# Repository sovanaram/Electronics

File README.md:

# Isolated Pure Sine Wave Single Phase Inverter using SPWM
this topic is about How to make Inverter by your self and These are the steps to makes it:
1, Researching theories of Inverter 
2, Select Topology (DCDC Converter stage, Inverter stage)
3, Calculating DCDC Converter and Inverter
4, Calculating Transformer and Inductors of DCDC Converter
5, Design Transformer and Inductors 
6, Design schematic and PCB 
7, Installing Hardware 
8, Select electronic switches(MOSFETs and DIODEs)
9, Select Controller
10, Programming and choose the types of Closed loop Control Methods, Filter
11, Testing Hardware

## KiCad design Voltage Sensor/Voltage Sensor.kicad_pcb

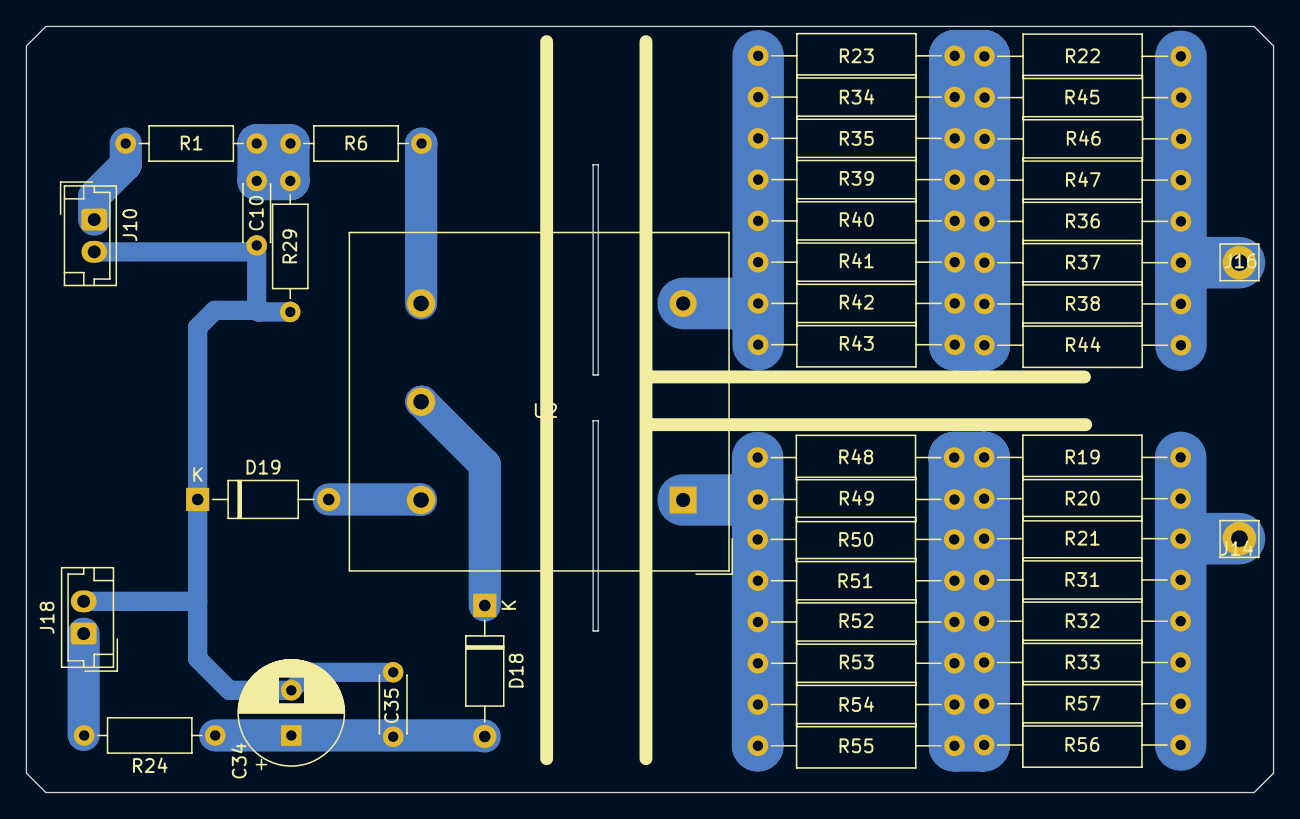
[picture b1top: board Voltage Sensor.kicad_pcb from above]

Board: 2 copper layers, 96.7 x 59.4 mm, 46 parts (0 on the bottom side), 4 nets.

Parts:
C10: 102; C_Disc_D4.3mm_W1.9mm_P5.00mm
C34: 100uF/25; CP_Radial_D8.0mm_P3.50mm
C35: 104; C_Disc_D4.3mm_W1.9mm_P5.00mm
D18: 1N4007; D_A-405_P10.16mm_Horizontal
D19: D; D_A-405_P10.16mm_Horizontal
J10: V_sens; JST_EH_B2B-EH-A_1x02_P2.50mm_Vertical
J14: 400VDC; Pin_D1.3mm_L11.3mm_W2.8mm_Flat
J16: GND; Pin_D1.3mm_L11.3mm_W2.8mm_Flat
J18: 12V_Vsens; JST_EH_B2B-EH-A_1x02_P2.50mm_Vertical
R1: 330; R_Axial_DIN0207_L6.3mm_D2.5mm_P10.16mm_Horizontal
R6, R29: 1K; R_Axial_DIN0207_L6.3mm_D2.5mm_P10.16mm_Horizontal
R19, R20, R21, R22, R23, R31, R32, R33, R34, R35, R36, R37, R38, R39, R40, R41, R42, R43, R44, R45, R46, R47, R48, R49, R50, R51, R52, R53, R54, R55, R56, R57: 100k; R_Axial_DIN0309_L9.0mm_D3.2mm_P15.24mm_Horizontal
R24: 100; R_Axial_DIN0207_L6.3mm_D2.5mm_P10.16mm_Horizontal
U2: LV25-P; LEM_LV25-P

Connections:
+12V: J18.1, R24.2
/+400VDC: J14.1, R19.2, R20.2, R21.2, R31.2, R32.2, R33.2, R56.2, R57.2
GND: C10.2, C34.2, C35.2, D19.1 (K), J10.2, J18.2, R29.1
GND1: J16.1, R22.2, R36.2, R37.2, R38.2, R44.2, R45.2, R46.2, R47.2

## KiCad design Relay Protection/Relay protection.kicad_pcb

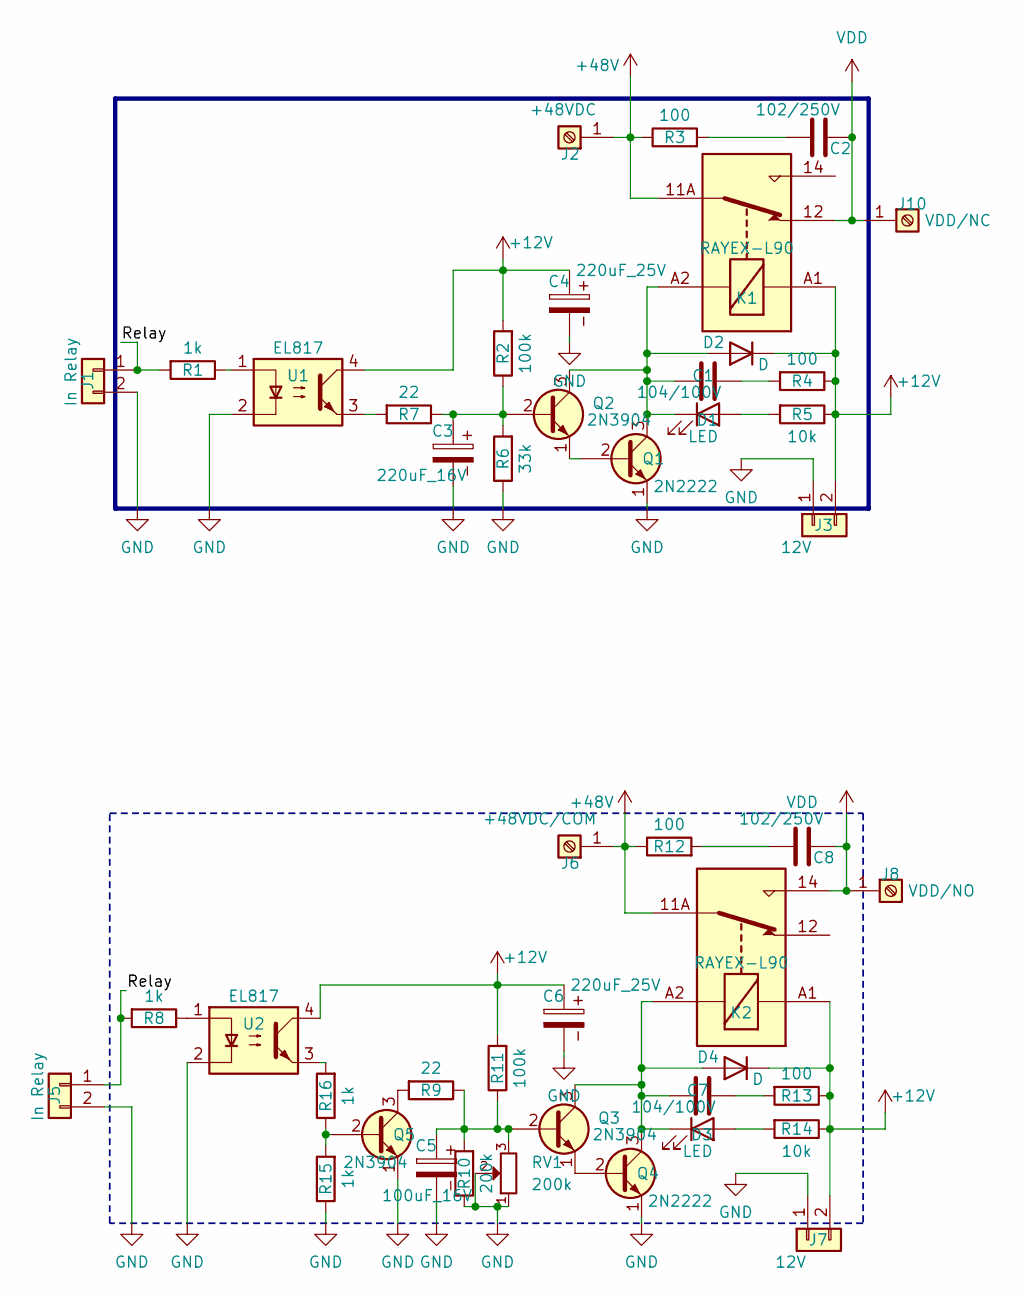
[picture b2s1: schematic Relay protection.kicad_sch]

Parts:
C1, C7: 104/100V; C_Disc_D6.0mm_W2.5mm_P5.00mm
C2, C8: 102/250V; Fuse_BelFuse_0ZRE0016FF_L9.9mm_W3.8mm
C3: 220uF_16V; CP_Radial_D6.3mm_P2.50mm
C4, C6: 220uF_25V; CP_Radial_D6.3mm_P2.50mm
C5: 100uF_16V; CP_Radial_D6.3mm_P2.50mm
D1, D3: LED; LED_D5.0mm_Clear
D2, D4: D; D_A-405_P10.16mm_Horizontal
J1, J5: In Relay; JST_EH_B2B-EH-A_1x02_P2.50mm_Vertical
J2: +48VDC; TerminalBlock_MetzConnect_360291_1x01_Horizontal_ScrewM3.0_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
J3, J7: 12V; JST_EH_B2B-EH-A_1x02_P2.50mm_Vertical
J6: +48VDC/COM; TerminalBlock_MetzConnect_360291_1x01_Horizontal_ScrewM3.0_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
J8: VDD/NO; TerminalBlock_MetzConnect_360291_1x01_Horizontal_ScrewM3.0_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
J10: VDD/NC; TerminalBlock_MetzConnect_360291_1x01_Horizontal_ScrewM3.0_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
K1, K2: RAYEX-L90; Relay_SPDT_RAYEX-L90
Q1, Q4: 2N2222; TO-92_Inline_Wide
Q2, Q3, Q5: 2N3904; TO-92L_Inline_Wide
R1, R8, R15, R16: 1k; R_Axial_DIN0207_L6.3mm_D2.5mm_P10.16mm_Horizontal
R2, R11: 100k; R_Axial_DIN0207_L6.3mm_D2.5mm_P10.16mm_Horizontal
R3, R4, R12, R13: 100; R_Axial_DIN0207_L6.3mm_D2.5mm_P10.16mm_Horizontal
R5, R14: 10k; R_Axial_DIN0207_L6.3mm_D2.5mm_P10.16mm_Horizontal
R6: 33k; R_Axial_DIN0207_L6.3mm_D2.5mm_P10.16mm_Horizontal
R7, R9: 22; R_Axial_DIN0207_L6.3mm_D2.5mm_P10.16mm_Horizontal
R10: 200k; R_Axial_DIN0207_L6.3mm_D2.5mm_P10.16mm_Horizontal
RV1: 200k; Potentiometer_RM065
U1, U2: EL817; DIP-4_W7.62mm

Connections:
+12V: C4.1, C6.1, D2.1 (K), D4.1 (K), J3.2, J7.2, K1.A1, K2.A1, R2.2, R4.1, R5.1, R11.2, R13.1, R14.1, U1.4, U2.4
+48V: J2.1, J6.1, K1.11A, K1.11B, K2.11A, K2.11B, R3.1, R12.1
/Relay: J1.1, J5.1, R1.2, R8.2
GND: C3.2, C4.2, C5.2, C6.2, J1.2, J3.1, J5.2, J7.1, Q1.1 (E), Q4.1 (E), Q5.1 (E), R6.1, R10.1, R15.1, RV1.1, RV1.2, U1.2, U2.2
unnamed: C1.1, R4.2
unnamed: C2.1, R3.2
unnamed: C7.1, R13.2
unnamed: C8.1, R12.2
unnamed: D1.2 (A), R5.2
unnamed: C1.2, D1.1 (K), D2.2 (A), K1.A2, Q1.3 (C), Q2.3 (C)
unnamed: D3.2 (A), R14.2
unnamed: C7.2, D3.1 (K), D4.2 (A), K2.A2, Q3.3 (C), Q4.3 (C)
unnamed: Q1.2 (B), Q2.1 (E)
unnamed: C3.1, Q2.2 (B), R2.1, R6.2, R7.1
unnamed: C5.1, Q3.2 (B), R9.1, R10.2, R11.1, RV1.3
unnamed: Q3.1 (E), Q4.2 (B)
unnamed: Q5.2 (B), R15.2, R16.1
unnamed: Q5.3 (C), R9.2
unnamed: R1.1, U1.1
unnamed: R7.2, U1.3
unnamed: R8.1, U2.1
unnamed: R16.2, U2.3
VDD: C2.2, C8.2, J8.1, J10.1, K1.12, K2.14

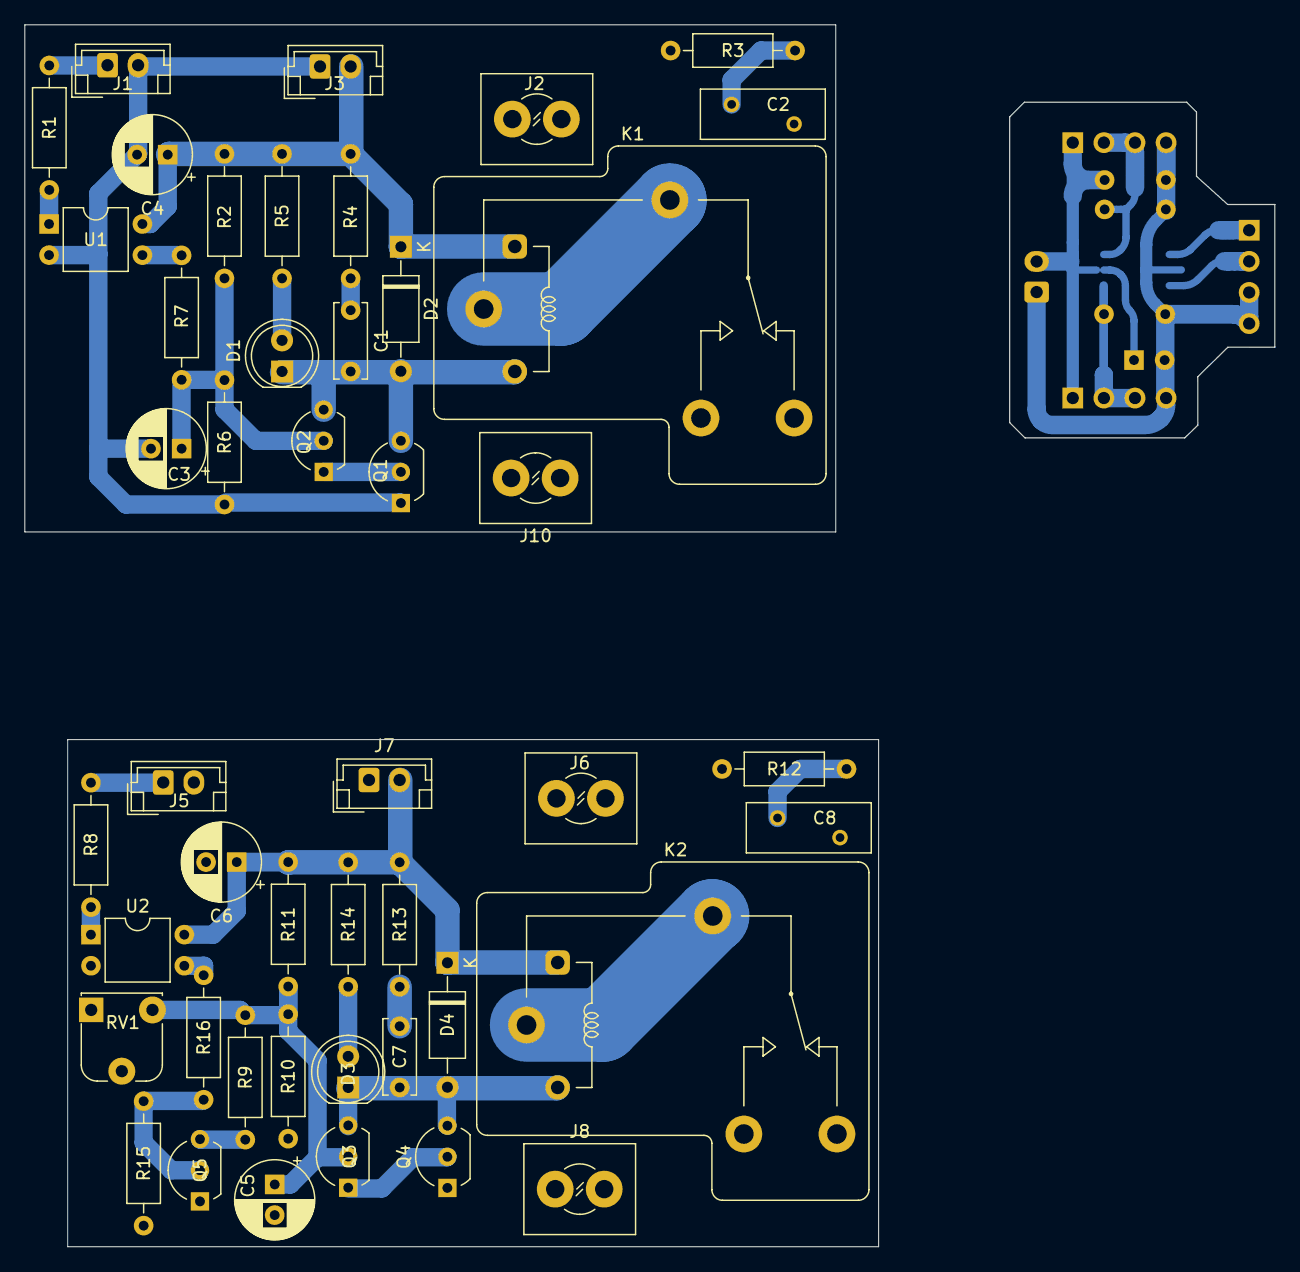
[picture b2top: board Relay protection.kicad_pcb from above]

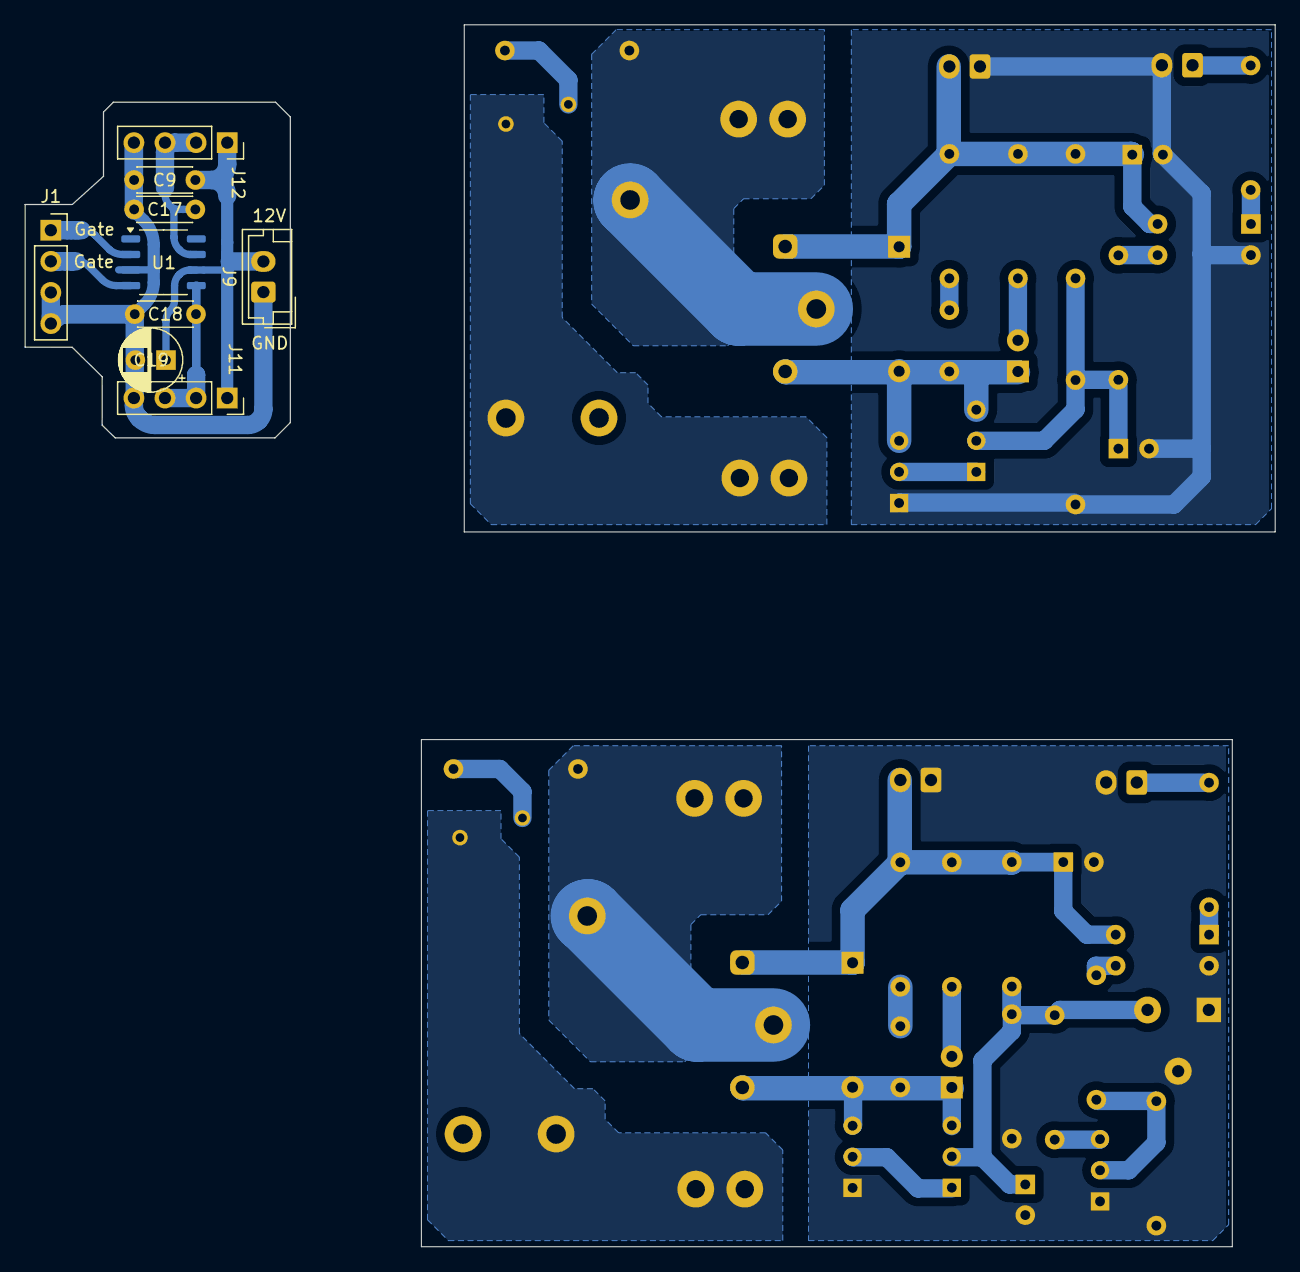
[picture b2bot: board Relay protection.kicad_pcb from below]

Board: 2 copper layers, 102.1 x 99.8 mm, 55 parts (9 on the bottom side), 23 nets.

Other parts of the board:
C9: 104; C_Disc_D4.3mm_W1.9mm_P5.00mm
C17, C18: 102; C_Disc_D4.3mm_W1.9mm_P5.00mm
C19: 10uF/50V; CP_Radial_D5.0mm_P2.50mm
J1#2, J11, J12: Conn_01x04; PinSocket_1x04_P2.54mm_Vertical
J9: 12V Gdriver; JST_EH_B2B-EH-A_1x02_P2.50mm_Vertical
U1#2: IRS4427S; SSOP-8_3.9x5.05mm_P1.27mm

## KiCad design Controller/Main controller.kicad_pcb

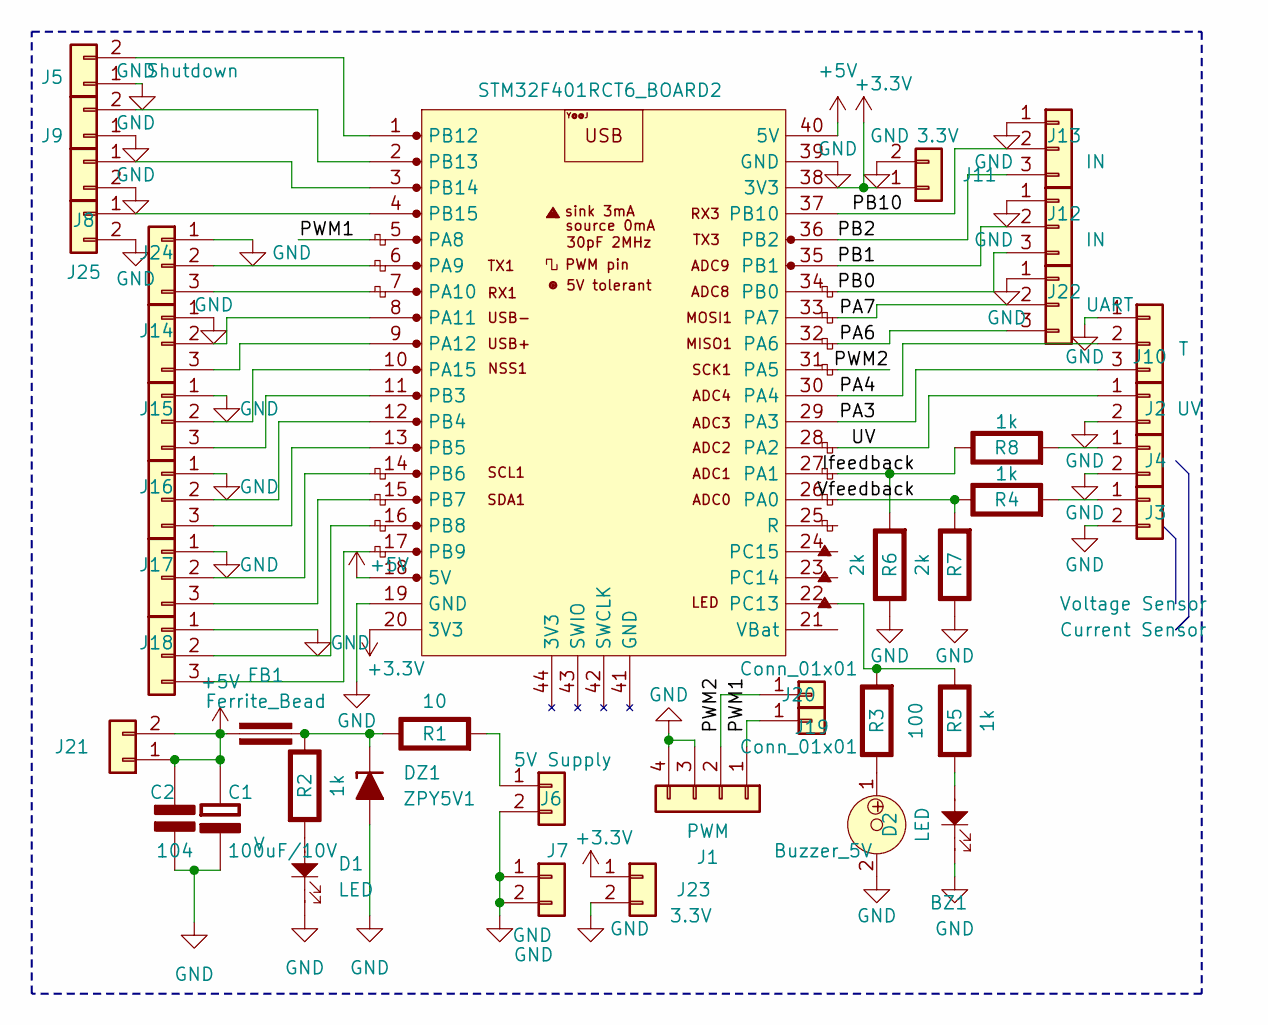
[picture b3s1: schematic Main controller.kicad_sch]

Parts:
BZ1: Buzzer_5V; MagneticBuzzer_ProSignal_ABT-410-RC
C1: 100uF/10V; CP_Radial_D7.5mm_P2.50mm; Rating V
C2: 104; C_Disc_D5.0mm_W2.5mm_P5.00mm; Rating V
D1, D2: LED; LED_D5.0mm
DZ1: ZPY5V1; D_DO-34_SOD68_P7.62mm_Horizontal
FB1: Ferrite_Bead; L_Axial_L7.0mm_D3.3mm_P5.08mm_Vertical_Fastron_MICC
J1: PWM; JST_EH_B4B-EH-A_1x04_P2.50mm_Vertical
J2: UV; JST_EH_B2B-EH-A_1x02_P2.50mm_Vertical
J3: Voltage Sensor; JST_EH_B2B-EH-A_1x02_P2.50mm_Vertical
J4: Current Sensor; JST_EH_B2B-EH-A_1x02_P2.50mm_Vertical
J5: Shutdown; JST_EH_B2B-EH-A_1x02_P2.50mm_Vertical
J6: 5V Supply; JST_EH_B2B-EH-A_1x02_P2.50mm_Vertical
J7: GND; JST_EH_B2B-EH-A_1x02_P2.50mm_Vertical
J8, J9, J21, J25: JST_EH_B2B-EH-A_1x02_P2.50mm_Vertical
J10: T; JST_EH_B3B-EH-A_1x03_P2.50mm_Vertical
J11, J23: 3.3V; JST_EH_B2B-EH-A_1x02_P2.50mm_Vertical
J12, J13: IN; JST_EH_B3B-EH-A_1x03_P2.50mm_Vertical
J14, J15, J16, J17, J18, J24: JST_EH_B3B-EH-A_1x03_P2.50mm_Vertical
J19, J20: Conn_01x01; PinSocket_1x01_P2.54mm_Vertical
J22: UART; JST_EH_B3B-EH-A_1x03_P2.50mm_Vertical
R1: 10; R_Axial_DIN0207_L6.3mm_D2.5mm_P10.16mm_Horizontal; Rating W
R2, R4, R5, R8: 1k; R_Axial_DIN0207_L6.3mm_D2.5mm_P10.16mm_Horizontal; Rating W
R3: 100; R_Axial_DIN0207_L6.3mm_D2.5mm_P10.16mm_Horizontal; Rating W
R6, R7: 2k; R_Axial_DIN0207_L6.3mm_D2.5mm_P10.16mm_Horizontal; Rating W
STM32F401RCT6_BOARD2: STM32F401RCT6_BOARD1

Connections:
+5V: C1.1 (+), C2.1 (+), FB1.1, J21.1, J21.2, STM32F401RCT6_BOARD2.18 (5V), STM32F401RCT6_BOARD2.40 (5V)
/Ifeedback: R6.2 (-), R8.1 (+), STM32F401RCT6_BOARD2.27 (PA1)
/PA3: J10.3, STM32F401RCT6_BOARD2.29 (PA3)
/PA4: J10.2, STM32F401RCT6_BOARD2.30 (PA4)
/PA6: J22.3, STM32F401RCT6_BOARD2.32 (PA6)
/PA7: J22.2, STM32F401RCT6_BOARD2.33 (PA7)
/PB0: J12.3, STM32F401RCT6_BOARD2.34 (PB0)
/PB1: J12.2, STM32F401RCT6_BOARD2.35 (PB1)
/PB2: J13.3, STM32F401RCT6_BOARD2.36 (PB2)
/PB10: J13.2, STM32F401RCT6_BOARD2.37 (PB10)
/PWM1: J1.1, J19.1, STM32F401RCT6_BOARD2.5 (PA8)
/PWM2: J1.2, J20.1, STM32F401RCT6_BOARD2.31 (PA5)
/UV: J2.1, STM32F401RCT6_BOARD2.28 (PA2)
/Vfeedback: R4.1 (+), R7.2 (-), STM32F401RCT6_BOARD2.26 (PA0)
GND: BZ1.2, C1.2 (-), C2.2 (-), D1.1, D2.1, DZ1.2 (A), J1.3, J1.4, J2.2, J3.2, J4.2, J5.1, J6.2, J7.1, J7.2, J8.2, J9.1, J10.1, J11.2, J12.1, J13.1, J14.1, J15.1, J16.1, J17.1, J18.1, J22.1, J23.2, J24.1, J25.2, R6.1 (+), R7.1 (+), STM32F401RCT6_BOARD2.19 (GND), STM32F401RCT6_BOARD2.39 (GND)
unnamed: DZ1.1 (K), FB1.2, R1.1 (+), R2.1 (+)
unnamed: J3.1, R4.2 (-)
unnamed: J4.1, R8.2 (-)
unnamed: J5.2, STM32F401RCT6_BOARD2.1 (PB12)
unnamed: J6.1, R1.2 (-)
unnamed: J8.1, STM32F401RCT6_BOARD2.3 (PB14)
unnamed: J9.2, STM32F401RCT6_BOARD2.2 (PB13)
unnamed: J14.2, STM32F401RCT6_BOARD2.8 (PA11)
unnamed: J14.3, STM32F401RCT6_BOARD2.9 (PA12)
unnamed: J15.2, STM32F401RCT6_BOARD2.10 (PA15)
unnamed: J15.3, STM32F401RCT6_BOARD2.11 (PB3)
unnamed: J16.2, STM32F401RCT6_BOARD2.12 (PB4)
unnamed: J16.3, STM32F401RCT6_BOARD2.13 (PB5)
unnamed: J17.2, STM32F401RCT6_BOARD2.14 (PB6)
unnamed: J17.3, STM32F401RCT6_BOARD2.15 (PB7)
unnamed: J18.2, STM32F401RCT6_BOARD2.16 (PB8)
unnamed: J18.3, STM32F401RCT6_BOARD2.17 (PB9)
unnamed: J24.2, STM32F401RCT6_BOARD2.6 (PA9)
unnamed: J24.3, STM32F401RCT6_BOARD2.7 (PA10)
unnamed: J25.1, STM32F401RCT6_BOARD2.4 (PB15)
unnamed: D1.2, R2.2 (-)
unnamed: BZ1.1, R3.1 (+)
unnamed: R3.2 (-), R5.1 (+), STM32F401RCT6_BOARD2.22 (PC13)
unnamed: D2.2, R5.2 (-)

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
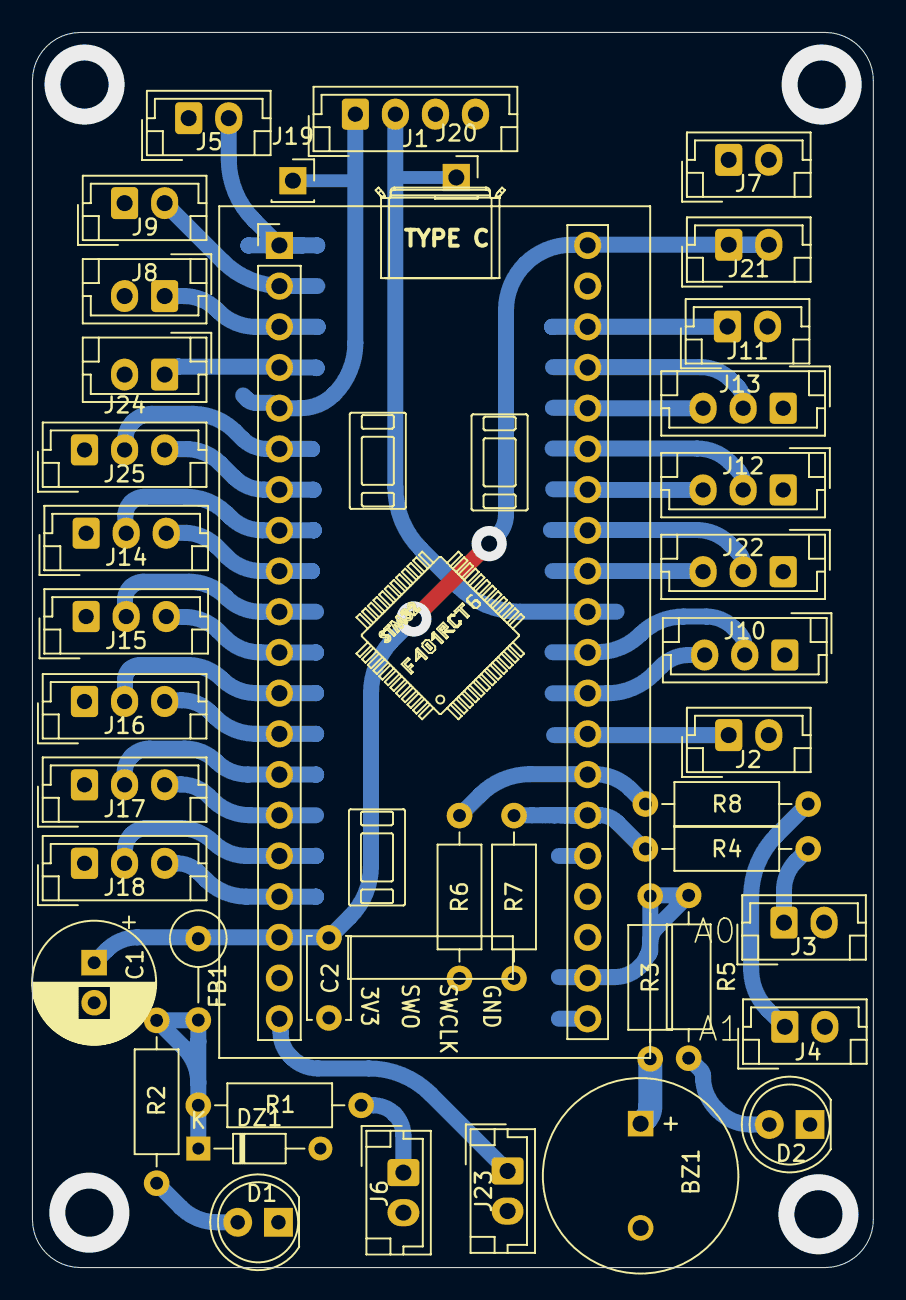
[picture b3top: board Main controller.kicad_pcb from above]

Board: 2 copper layers, 52.5 x 77.1 mm, 41 parts (0 on the bottom side), 41 nets.

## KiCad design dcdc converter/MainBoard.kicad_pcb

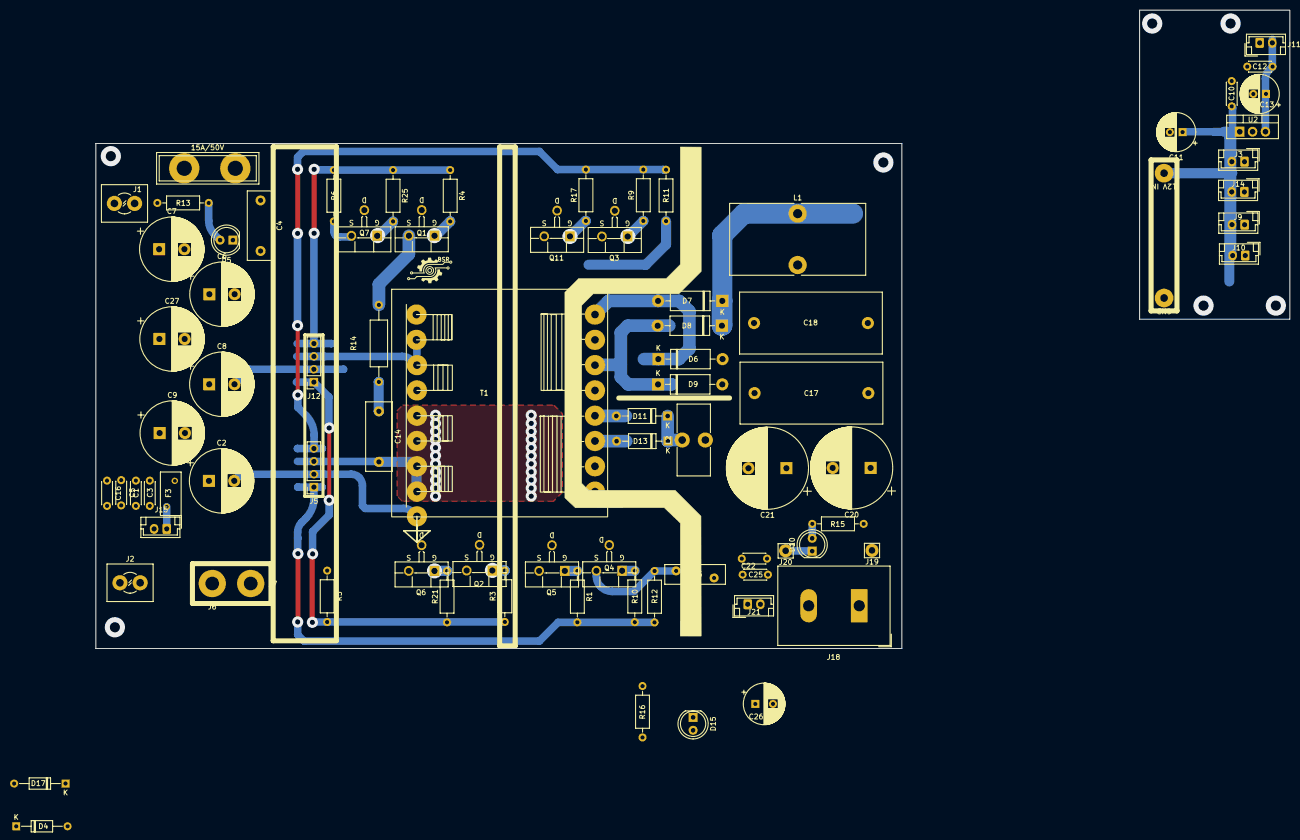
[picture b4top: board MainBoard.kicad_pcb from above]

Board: 2 copper layers, 236.1 x 126.2 mm, 84 parts (0 on the bottom side), 35 nets.

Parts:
BSR: LOGO
C1, C3, C5, C10, C12, C16, C22, C25: 104; C_Disc_D4.3mm_W1.9mm_P5.00mm
C2, C6, C7, C8, C9, C27: 1000uF/50V; CP_Radial_D12.5mm_P5.00mm
C4, C14: 102/250V; C_Rect_L13.5mm_W5.0mm_P10.00mm_FKS3_FKP3_MKS4
C11: 100uF/25V; CP_Radial_D7.5mm_P2.50mm
C13: 220uF/10V; CP_Radial_D7.5mm_P2.50mm
C15: 102/1KV; RV_Disc_D12mm_W3.9mm_P7.5mm
C17, C18: 105/630V; C_Rect_L28.0mm_W12.0mm_P22.50mm_MKS4
C20, C21: 10uF/250V; CP_Radial_D16.0mm_P7.50mm
C26: 100uF/50V; CP_Radial_D8.0mm_P3.50mm
D4, D17: 1N4148; D_DO-35_SOD27_P10.16mm_Horizontal
D5, D10, D15: LED; LED_D5.0mm_Clear
D6, D7, D8, D9: MUR460; D_DO-15_P12.70mm_Horizontal
D11, D13: 1N5819; D_A-405_P10.16mm_Horizontal
F1: 15A/50V; fuse15A
F3: 0.75A/50V; Fuse_BelFuse_0ZRE0012FF_L8.3mm_W3.8mm
J1: +48VDC; TerminalBlock_MetzConnect_360291_1x01_Horizontal_ScrewM3.0_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
J2: GND; TerminalBlock_MetzConnect_360291_1x01_Horizontal_ScrewM3.0_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
J3, J9, J10, J14: 12V; JST_EH_B2B-EH-A_1x02_P2.50mm_Vertical
J5: Gate2; PinSocket_1x04_P2.54mm_Vertical
J6: GND; MountingHole_2.7mm_M2.5_Pad
J7: GNDsens; MountingHole_2.7mm_M2.5_Pad
J11: 5V; JST_EH_B2B-EH-A_1x02_P2.50mm_Vertical
J12: Gate1; PinSocket_1x04_P2.54mm_Vertical
J15: 48VDC; JST_EH_B2B-EH-A_1x02_P2.50mm_Vertical
J16: GND; 3.7mm Pin
J17: 12V IN; 3.7mm Pin
J18: 400VDC OUT; TerminalBlock_Dinkle_DT-55-B01X-02_P10.00mm
J19: 400VDC; Pin_D1.3mm_L11.3mm_W2.8mm_Flat
J20: GND; Pin_D1.3mm_L11.3mm_W2.8mm_Flat
J21: 24VDC; JST_EH_B2B-EH-A_1x02_P2.50mm_Vertical
L1: 3mH; L_Toroid_Vertical_L26.7mm_W14.0mm_P10.16mm_Pulse_D
L2: 100uH; L_Toroid_Vertical_L14.0mm_W6.3mm_P4.57mm_Pulse_A
Q1, Q2, Q3, Q4, Q5, Q6, Q7, Q11: IRFB4310; TO-220F-3_Staggered_Vertical_GDS
R1, R3, R4, R9, R10, R17, R21, R25: 10; R_Axial_DIN0207_L6.3mm_D2.5mm_P10.16mm_Horizontal
R5, R6, R11, R12, R13, R16: 10K; R_Axial_DIN0207_L6.3mm_D2.5mm_P10.16mm_Horizontal
R14: 330/1W; R_Axial_DIN0309_L9.0mm_D3.2mm_P15.24mm_Horizontal
R15: 100K; R_Axial_DIN0207_L6.3mm_D2.5mm_P10.16mm_Horizontal
T1: PQ3535
U2: L7805; TO-220-3_Vertical

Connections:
+5V: C12.2, C13.1, J11.2, U2.3 (OUT)
+12V: C10.2, C11.1, J3.2, J9.2, J10.2, J14.2, J17.1, U2.1 (IN)
+24V: C22.1, C25.1, C26.1, J21.1, L2.2, R16.1
/+48V In: C1.1, C3.1, C5.1, C7.1, C9.1, C16.1, C27.1, F1.1, F3.2, J1.1, R13.1
/+400VDC: C17.1, C18.1, C20.1, J18.1, J19.1, L1.2, R15.1
/GH1: J12.4, R4.1, R6.2, R25.1
/GH2: J5.4, R9.2, R11.2, R17.2
/GL1: J12.1, R3.1, R5.2, R21.1
/GL2: J5.1, R1.2, R10.2, R12.2
/VS1: C14.2, J5.3, J12.3, Q1.3 (S), Q2.2 (D), Q3.3 (S), Q4.2 (D), Q5.2 (D), Q6.2 (D), Q7.3 (S), Q11.3 (S), R6.1, R11.1, R14.2, T1.1, T1.2, T1.3, T1.4, T1.5, T1.6, T1.7, T1.8
GND: C1.2, C2.2, C3.2, C4.2, C5.2, C6.2, C8.2, C10.1, C11.2, C12.1, C13.2, C15.1, C16.2, D5.1 (K), J3.1, J5.2, J7.1, J9.1, J10.1, J11.1, J12.2, J14.1, J15.2, J16.1, Q2.3 (S), Q4.3 (S), Q5.3 (S), Q6.3 (S), R5.1, R12.1, T1.17 (GND), U2.2 (GND)
GND1: C15.2, C17.2, C18.2, C21.2, C22.2, C25.2, C26.2, D6.2 (A), D9.2 (A), D10.1 (K), D15.1 (K), J18.2, J20.1, J21.2, T1.10
unnamed: C2.1, C6.1, C7.2, C8.1, C9.2, C27.2
unnamed: C14.1, R14.1
unnamed: C20.2, C21.1
unnamed: D5.2 (A), R13.2
unnamed: D6.1 (K), D7.2 (A), T1.16
unnamed: D7.1 (K), D8.1 (K), L1.1
unnamed: D8.2 (A), D9.1 (K), T1.14
unnamed: D10.2 (A), R15.2
unnamed: D11.2 (A), T1.12
unnamed: D11.1 (K), D13.1 (K), L2.1
unnamed: D13.2 (A), T1.11
unnamed: D15.2 (A), R16.2
unnamed: J2.1, J6.1
unnamed: F3.1, J15.1
unnamed: Q1.1 (G), R4.2
unnamed: Q2.1 (G), R3.2
unnamed: Q3.1 (G), R9.1
unnamed: Q4.1 (G), R10.1
unnamed: Q5.1 (G), R1.1
unnamed: Q6.1 (G), R21.2
unnamed: Q7.1 (G), R25.2
unnamed: Q11.1 (G), R17.1
VDD: C4.1, F1.2, Q1.2 (D), Q3.2 (D), Q7.2 (D), Q11.2 (D)

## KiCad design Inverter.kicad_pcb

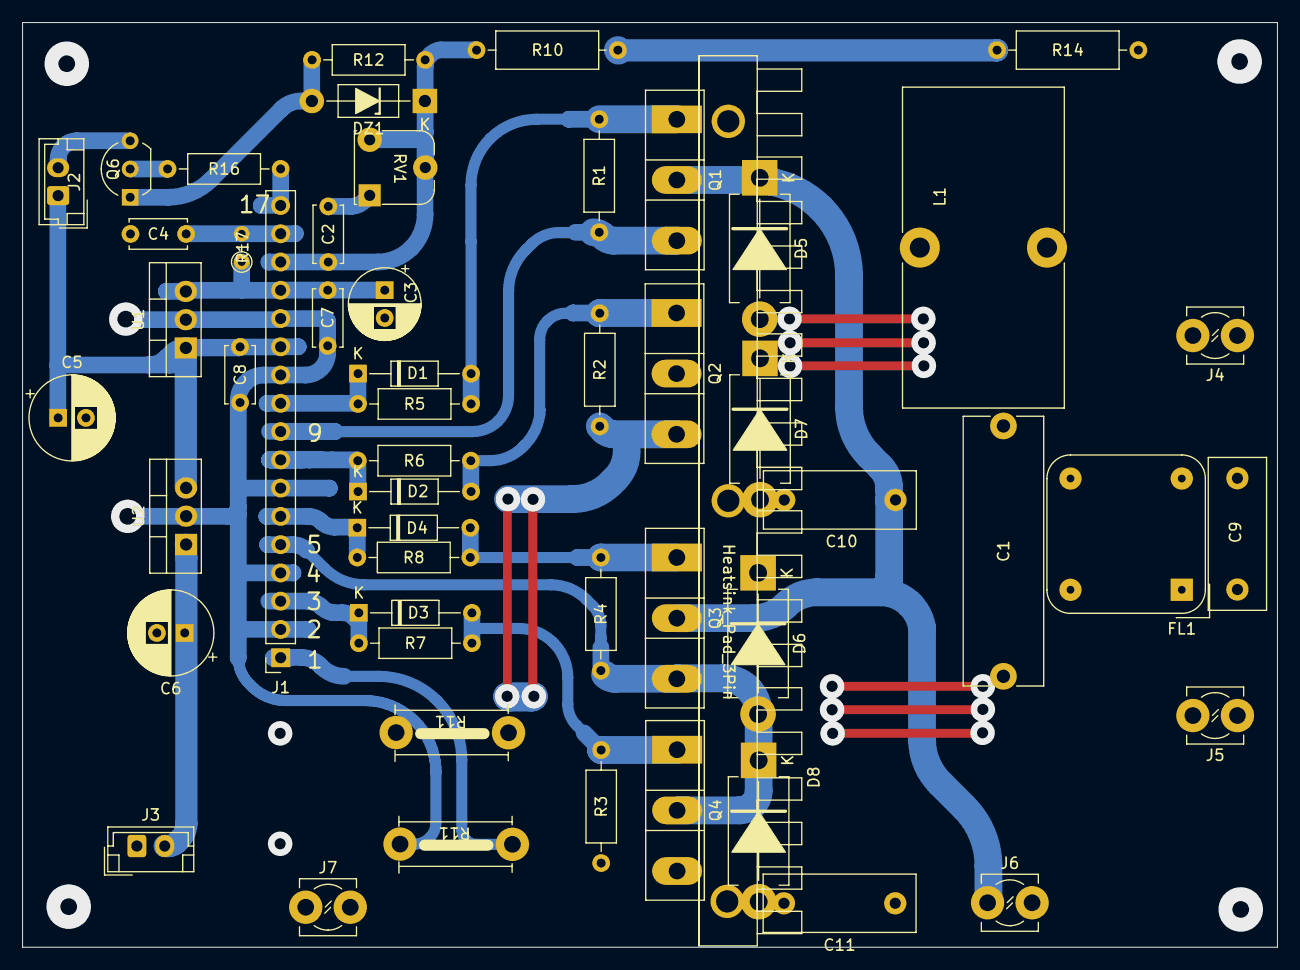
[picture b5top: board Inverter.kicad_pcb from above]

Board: 2 copper layers, 112.8 x 83.1 mm, 53 parts (0 on the bottom side), 25 nets.

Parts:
C1: 225/400V; C_Rect_L24.0mm_W7.0mm_P22.50mm_MKT
C2, C7, C8: 104; C_Disc_D5.0mm_W2.5mm_P5.00mm
C3: 220uF/10V; CP_Radial_D6.3mm_P2.50mm
C4: 103; C_Disc_D5.0mm_W2.5mm_P5.00mm
C5: 100uF/25V; CP_Radial_D7.5mm_P2.50mm
C6: 330uF/35V; CP_Radial_D7.5mm_P2.50mm
C9, C10, C11: 0.1u/275V; C_Rect_L13.5mm_W5.0mm_P10.00mm_FKS3_FKP3_MKS4
D1, D2, D3, D4: 1N4148; D_DO-35_SOD27_P10.16mm_Horizontal
D5, D6, D7, D8: MUR460; D_DO-201AD_P12.70mm_Horizontal
DZ1: BZD23-C5V1; D_DO-41_SOD81_P10.16mm_Horizontal_Zener
FL1: Filter_EMI_LL; Choke_Schaffner_RN102-04-14.0x14.0mm
HS1: Heatsink_Pad_3Pin; heatsink
J1: EGS002; PinSocket_1x17_P2.54mm_Vertical
J2: FAN; JST_EH_B2B-EH-A_1x02_P2.50mm_Vertical
J3: Vin; JST_EH_B2B-EH-A_1x02_P2.50mm_Vertical
J4: L; TerminalBlock_MetzConnect_360381_1x01_Horizontal_ScrewM3.0
J5: N; TerminalBlock_MetzConnect_360381_1x01_Horizontal_ScrewM3.0
J6: VDD; TerminalBlock_MetzConnect_360381_1x01_Horizontal_ScrewM3.0
J7: GND; TerminalBlock_MetzConnect_360381_1x01_Horizontal_ScrewM3.0
L1: 3.3mH; L_Toroid_Vertical_L28.6mm_W14.3mm_P11.43mm_Bourns_5700
Q1, Q2, Q3, Q4: FGH40N60SFD; TO-247-3_Vertical
Q6: 2N2222A; TO-92_Inline_Wide
R1, R2, R3, R4, R12: 10k; R_Axial_DIN0207_L6.3mm_D2.5mm_P10.16mm_Horizontal
R5, R6, R7, R8: 4.7; R_Axial_DIN0207_L6.3mm_D2.5mm_P10.16mm_Horizontal
R10, R14: 100K; R_Axial_DIN0309_L9.0mm_D3.2mm_P12.70mm_Horizontal
R11, R11#2: 0.4; shun_L10mm
R16: 2.2K; R_Axial_DIN0207_L6.3mm_D2.5mm_P10.16mm_Horizontal
R17: NTC/10K; R_Axial_DIN0204_L3.6mm_D1.6mm_P2.54mm_Vertical
RV1: 10K; Potentiometer_RM065
U1: L7805; TO-220-3_Vertical
U2: L7812; TO-220-3_Vertical

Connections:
+5V: C3.1, C7.1 (+), J1.14, R17.1 (+), U1.3 (OUT)
+12V: C5.1, C8.1 (+), J1.12, J2.1, U1.1 (IN), U2.3 (OUT)
+VDC 400V: C10.1 (+), C11.1 (+), D5.1 (K), D6.1 (K), J6.1, Q1.2 (C), Q3.2 (C)
/FANCTR: J1.17, R16.1 (+)
/HO1: D4.1 (K), J1.6, R8.1 (+)
/HO2: D1.1 (K), J1.10, R5.1 (+)
/IFB: C10.2 (-), C11.2 (-), D7.2 (A), D8.2 (A), HS1.1, HS1.2, HS1.3, J1.1, Q2.3 (E), Q4.3 (E), R2.2 (-), R3.2 (-), R11.1, R11.2, R11#2.1, R11#2.2
/L: C9.1 (+), FL1.3, J4.1, R14.1 (+)
/LO1: D3.1 (K), J1.3, R7.1 (+)
/LO2: D2.1 (K), J1.8, R6.1 (+)
/N: C9.2 (-), FL1.1, J5.1
/TFB: C4.1 (+), J1.16, R17.2 (-)
/VFB: C2.1 (+), DZ1.1 (K), J1.15, R10.2 (-), R12.1 (+), RV1.2, RV1.3
/VS1: C1.2 (-), D6.2 (A), D8.1 (K), FL1.2, J1.5, Q3.3 (E), Q4.2 (C), R4.2 (-)
/VS2: D5.2 (A), D7.1 (K), J1.9, L1.1, Q1.3 (E), Q2.2 (C), R1.2 (-)
/Vin_supply: C6.1, J3.2, U2.1 (IN)
GND: C2.2 (-), C3.2, C4.2 (-), C5.2, C6.2, C7.2 (-), C8.2 (-), DZ1.2 (A), J1.2, J1.4, J1.7, J1.11, J1.13, J3.1, J7.1, Q6.1 (E), R11.3, R11.4, R11#2.3, R11#2.4, R12.2 (-), RV1.1, U1.2 (GND), U2.2 (GND)
unnamed: C1.1 (+), FL1.4, L1.2
unnamed: D1.2 (A), Q1.1 (G), R1.1 (+), R5.2 (-)
unnamed: D2.2 (A), Q2.1 (G), R2.1 (+), R6.2 (-)
unnamed: D3.2 (A), Q4.1 (G), R3.1 (+), R7.2 (-)
unnamed: D4.2 (A), Q3.1 (G), R4.1 (+), R8.2 (-)
unnamed: J2.2, Q6.3 (C)
unnamed: Q6.2 (B), R16.2 (-)
unnamed: R10.1 (+), R14.2 (-)
